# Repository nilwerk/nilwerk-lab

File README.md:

# nilwerk-lab

Engineering workspace for Nilwerk's agent team. Private.

- **How the team works:** [`team/TEAM.md`](team/TEAM.md) — roles, daily cycle, Definition of Done, hard rules.
- **Roles:** [`team/roles/`](team/roles/)
- **Daily reports:** [`team/reports/`](team/reports/)
- **First project:** [`projects/plant-monitor/`](projects/plant-monitor/) — task status lives in the Google Sheet *Plant Monitor – Project Plan*, not here.

Agents work on `agent/<role>/<task-id>` branches and open PRs. Only Arsany merges to `main`.

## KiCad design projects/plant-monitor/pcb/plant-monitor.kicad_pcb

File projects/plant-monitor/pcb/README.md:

# PCB (Plan 4.P1: schematic) — Emil (PCB Designer)

KiCad 9 project `plant-monitor.kicad_pro` / `plant-monitor.kicad_sch` (one A1 sheet, net labels at every pin, no wires).
It is **generated** from [`design.py`](design.py) by [`gen_schematic.py`](gen_schematic.py) (no GUI was available);
[`check_netlist.py`](check_netlist.py) is the independent netlist/BOM/sleep check. Requirements: NFR-01 (best and typical case >= 3 months, worst case > 1 month; relaxed by Arsany 2026-11-08), NFR-12 (<= 50 uA, target 25 uA, A-027).
Layout is 4.P2, **slice 1 done (placement, not routed), slice 2 done (real footprints for U1/J1/J2/SW/standard parts, vias out of pads, antenna check in CI), slice 3 done (U5/U6 footprints from LCSC/EasyEDA data, power section routed except 3 connections; signal routing, GND pour and 3V3 distribution still open, not fab-ready)**: see [`layout-4P2.md`](layout-4P2.md); the board is generated by [`gen_pcb.py`](gen_pcb.py), checked by [`check_layout.py`](check_layout.py). Nothing was ordered.

**Update 2026-11-08 (Arsany's answers):** A-034 the cell is the **EEMB LP603449-PCM from Amazon.de (ASIN B08FD39Y5R)**; NFR-01 relaxed; **A-045 Option A** and **A-046 Option A** applied (below). Cell facts and what is still unverified: [`../hardware/bom/cell-decision-A034.md`](../hardware/bom/cell-decision-A034.md).

## Status of the checks

| Check | Result |
|---|---|
| KiCad ERC (`kicad-cli sch erc`) | Runs in CI (job `pcb`, KiCad 9 container) on every push of this PR; not available in the agent session. 0 violations at error level on head a0a4c90, CI run 42576375828 (job `pcb`, job 129024963788). |
| `python3 -I check_netlist.py` | all PASS (nets rebuilt from the file = model, no unconnected pin, no 1-pin net, BOM draft lcsc/qty = schematic, R9, strap pins, sleep sum) |
| KiCad DRC (`kicad-cli pcb drc`) | CI job `pcb`: 0 violations at error level on the 4.P2 slice-1 head (placed, not routed, placeholder footprints; unconnected items are warning-level, not in the error-level report; `unconnected_items` = warning, to be reverted when routing starts): [`layout-4P2.md`](layout-4P2.md). |
| `/usr/bin/python3 -I check_layout.py` | 18/18 PASS (own geometry check of the board file, not KiCad DRC) |
| Simulations | **LDO dropout: RUN** (ngspice 42 via `apt-get install ngspice`, `sim/ldo_dropout.py`, `sim/ldo_dropout.png`): V(3V3) stays >= 3.05 V in every modelled case at the 3.4 V warning point (limit 3.0 V = VDD33 min), fails at <= 3.3 V cell with 0.30 ohm / pessimistic dropout, see `layout-brief.md` section 6. Divider, soil front end, charger thresholds, USB inrush: **NOT RUN.** |

## Charge current R9 (A-034 decided 2026-11-08)

Cell: EEMB LP603449-PCM, 1000 mAh minimum (1100 typical), maximum charging current 1100 mA, charge 0 to 45 C (Amazon.de listing, A+ text). `design.py` block `CHARGE CURRENT`: `CELL_MIN_MAH`, `CELL_MAX_CHARGE_MA`, `R9_OHM`, `R9_LCSC`. Recomputed for this cell: R_PROG = 1100 / I_BAT (TP4056 datasheet p. 9), target <= 0.5C = 500 mA. **R9 stays 2.4k (C22940): 458 mA = 0.46C of the minimum capacity (0.42C of typical); with the TP4056's +15 % tolerance 527 mA = 0.53C, below the 1100 mA cell maximum.** 2.2k would give exactly 0.50C (500 mA) but its LCSC number is not looked up and the USB 2.0 budget (500 mA, open point 3) has no room for it. USB draw is about 458 + 10 mA with no power path (A-046): inside 500 mA nominally; at +15 % tolerance (527 mA) the port limit is exceeded, accepted risk, see open point 3. `check_netlist.py` asserts <= 0.5C and tolerance <= cell maximum.

## Cell connector, NTC / TEMP (decided cell)

J2 = JST PH 2-pin (C295747): pin 1 = CELL+ (VBAT), pin 2 = CELL- (CELL_NEG). The listing says "JST plug" (picture 3 shows it) but **does not state the pitch or the polarity**: PH 2.0 mm is assumed and **unverified**; read it off the plug or the listing photo before ordering mating parts. An Amazon review of this listing reports a reversed plug: **check polarity with a meter before the first connection.** The listing mentions no NTC, so **TP4056 TEMP stays tied to GND (sense disabled, datasheet p.7)** and cold/hot charging (0 to 45 C only) is not enforced by the board. The Jauch 3-pin variant J2b (C564183) is not used.

## Sleep-current path and pin map

Generated: [`pinmap-sleep.md`](pinmap-sleep.md). Typical **21.6 uA**, worst **39.6 uA** vs NFR-12 25 / 50 uA (after A-045: +2.1 uA permanent divider), mostly assumptions.

## Differences against the BOM draft (hardware/bom)

**Synced 2026-11-08 (branch `agent/pcb/bom-sync`):** `hardware/bom/bom-draft.csv` now has Q2 deleted, R3-R5 qty 3, R13/R14 (4.7k I2C), R15 (1k DW01A CS), R16 (10k GPIO2) and B1 = the decided EEMB LP603449-PCM; `check_netlist.py` has no declared differences left (every LCSC number and quantity equals the schematic, and `bom.csv` equals the schematic). Footprints for SW1-3, U5, U6, E1 are custom names still to be drawn.

## Open points

1. ~~Battery sense, Q2 off: BAT_SENS floats to VBAT~~ **Closed (A-045 Option A, Arsany 2026-11-08):** Q2 and R6 dropped, R7/R8 1M+1M permanent divider (2.1 uA at 4.2 V), BAT_SENS never above 2.1 V, IO1 free.
2. **TEMP / cold charging:** cell may be charged 0-45 C only; the decided cell lists no NTC, TEMP grounded. Mitigation options: a GPIO on CE (CE internal default not read) or accept (indoor charging).
3. **USB 500 mA:** 458 mA charge + board load is at the USB 2.0 limit; TP4056 dissipates 0.78 W at 5 V in / 3.3 V cell (thermal foldback, not simulated).
4. **Double protection (decision for Arsany, recommendation: delete U4/Q1/R15/C9 once the PCM on the received cell is confirmed).** Numbers (`hardware/bom/bom_calc.py` variant D, live prices 2026-11-08): saves 2 Extended parts and 4 pieces; BOM at 3 boards 20.04 -> 17.86 USD/board (-2.18, of which -2.05 is JLC loading fee 2 x 3.07 / 3, -0.13 parts), at 1k boards 4.05 -> 3.96 (-0.09; U4 0.017 + Q1 0.060 + R15 0.001 + C9 0.009 USD at the 1k price breaks). Sleep: -3.05 uA typ (DW01A 3 + 8205A 0.05, both assumptions, datasheet Iq not read) and -7 uA worst: 21.6 -> 18.6 uA typ, 39.6 -> 32.6 uA worst (NFR-12 target 25 uA gets 1.35x margin instead of 1.16x). Battery life: about +1 % (typical 4.3 -> 4.35 months, worst +0.01), small. Also removes a series Rds(on) (8205A, value unread) from the 350 mA TX path = better LDO headroom. Risk of deleting: the cell's PCM exists only as a listing claim (OC/OD/over-current/short; thresholds, PCM IC, IEC 62133 not stated; one review reports a reversed plug, so QC varies); a second protection is the only protection if that PCM is faulty or missing, and a lithium pouch without any protection is a fire risk. Why not done now: not clearly safe without the cell in hand (nobody has read the PCM board or tested its cutoffs), and it is Arsany's call. Recommended path: keep v1 schematic and layout unchanged for the first 3 prototypes (no layout exists yet, so deleting later costs one regenerate + one BOM line change), Peter reads the PCM marking and measures over-discharge cutoff and short-circuit trip on one cell (5.x), then delete for the 1k design. If Arsany wants it deleted now: remove U4, Q1, R15, C9 in `design.py` and tie CELL_NEG to GND (about 20 min incl. regenerate and checks).
5. ~~GPIO2 strap left unconnected~~ **Closed (Theo C4):** R16 10k to 3V3 on GPIO2 (Espressif datasheet v2.2 s.4.1 recommends a pull-up). No sleep current.
6. **USB data:** BOM says "power only"; D+/D- are wired to IO19/IO18 (USB Serial/JTAG) so D1 is meaningful. Arsany/Mira to confirm (affects flashing).
7. **Pin numbers: all now checked against datasheets** (see Fix round). Remaining: BH1750 DVI is tied directly to VCC; the datasheet wants DVI low >= 1 us after VCC (reset), example RC 1k/1uF. Decide in 4.P2 (add RC or accept and re-init in firmware).
8. Soil: electrode capacitance still assumed, no electrode ESD, wet/salty soil loading, U7 supply GPIO must be held low in deep sleep (firmware).
9. No power path (**A-046 Option A, Arsany 2026-11-08: accepted for v1; the board needs a cell**, document in the user guide: with USB only and no cell it does not run, and "charge complete" can be late while Wi-Fi is active): No VBUS fuse/TVS (only USBLC6). No DW01A VCC filter resistor. No VBUS-present or CHRG sense to a GPIO.
10. LDO Iq is 8 uA typ (datasheet, PS mode, 0.1 mA load; 18 uA max), 6 uA above the power-budget typical (2 uA, assumption A). Cost: 6 uA x 24 h = 0.144 mAh/day (about 53 mAh/year). The sleep sum in `pinmap-sleep.md` already uses 8 uA. `hardware/power-budget` keeps its 2 uA baseline rows; since 2026-11-08 it also has "as-built sleep" rows (LDO 8 uA, divider 2.1 uA, same sums as `pinmap-sleep.md`), see power-budget.md section 12.
11. ~~Cell A-034 decision~~ **Closed 2026-11-08:** EEMB LP603449-PCM; R9 recomputed (stays 2.4k). `firmware/main/board.h` does not exist; this pin table is the proposal. **IO1 is free (was BAT_SENS_EN): Mira must not drive it as a divider switch.**

## Fix round for Theo's review (PR #41, C1-C8)

| Item | Result |
|---|---|
| C1 AHT20 U5 | LCSC C2757850 resolved through the LCSC API (`wmsc.lcsc.com`) and its datasheet (Aosong/ASAIR, 2024-07, Table 5 and Figure 1): **6-pin DFN 3.0 x 3.0 x 1.0 mm**, 1 NC, 2 VDD, 3 SCL, 4 SDA, 5 GND, 6 NC. Symbol fixed (`design.py`), `pin_verified` now true, checked by `check_netlist.py`. Footprint `NW:AHT20_DFN-6_3x3` still to be drawn in 4.P2. Stock 32649 at the time of the call. |
| C2 pins | Read from the LCSC-linked datasheets: **U2** XC6220 SOT-25 (VIN 1, VSS 2, CE 3, NC 4, VOUT 5), **U4** DW01A (1 OD, 2 VM = CS, 3 OC, 4 TD, 5 VCC, 6 GND), **Q1** 8205A TSSOP-8 (package drawing: 1 D1, 2-3 S1, 4 G1, 5 G2, 6-7 S2, 8 D2; no numbered table in the datasheet, read from the drawing), **U6** BH1750 (1 VCC, 2 ADDR, 3 GND, 4 SDA, 5 DVI, 6 SCL), **J1** HRO TYPE-C-31-M-12 (signal-to-pad table; shield pad numbers belong to the footprint). Also checked: U3 TP4056 (1 TEMP, 2 PROG, 3 GND, 4 VCC, 5 BAT, 6 STDBY, 7 CHRG, 8 CE), U7 SN74LVC1G14 DBV (1 NC, 2 A, 3 GND, 4 Y, 5 VCC), D1 USBLC6-2SC6. All match the schematic. U1 was verified by Theo. `pin_verified=False` was gone from every part after 4.P1; 4.P2 sets it again for SW1-SW3, U5, U6, J1 until the placed footprints are compared with the drawings (`layout-4P2.md`). |
| C4 GPIO2 | R16 10k 3V3 to GPIO2 added (declared addition, BOM qty of C25804 5). |
| C5 LDO dropout sim (superseded by the next row) | *Original first-pass status, kept for traceability:* not run at the time, hand estimate only: datasheet gives 60 mV typ dropout at 300 mA (3.3 V version; the table row is ambiguous), the 3.4 V warning leaves 100 mV, so at a ~350 mA TX peak typ headroom is about 30 mV before the cell resistance drop (0.15 ohm x 0.35 A = 52 mV, assumed). That is negative margin: the rail may sag to roughly 3.25-3.3 V, which stays above the C3 brown-out level but this needs the real sim and the real cell resistance (4.P3). Do not take the estimate as a pass. LDO Iq 8 uA vs 2 uA in the budget: see open point 10. |
| C5 follow-up 2026-11-08 | Simulated: the hand estimate's conclusion (rail below 3.3 V) is right but the limit is 3.0 V, and the margin there is +0.05 to +0.27 V at 3.4 V cell voltage (`sim/ldo_dropout.txt`). |
| C8 caption | Corrected (6.3 agent min, PR link, persona, no ratio). |
| C3, C6 | Decisions below, not changed. |

## Decisions (answered by Arsany 2026-11-08)

**D-C3 / A-045: ANSWERED 2026-11-08, Option A approved.** Q2 and R6 dropped, R7/R8 1M+1M stay as a permanent divider (4.2 V / 2 MOhm = 2.1 uA, about 0.05 mAh/day; total typical 21.6 uA under the 25 uA target, worst 39.6 uA under the 50 uA NFR-12 limit). BAT_SENS never exceeds 2.1 V on IO0; IO1 is free. Applied in `design.py`, the schematic, `bom.csv`, `pinmap-sleep.md`. (Option B, a high-side P-FET switch, was not chosen.)

**D-C6 / A-046: ANSWERED 2026-11-08, Option A approved.** No power path in v1. **The board needs a cell to run** (USB alone, with no cell connected, does not power it reliably, and charge termination can be late while the board is awake and drawing current; the sleep load of about 22 uA is far below the TP4056 termination threshold of about 46 mA, so it matters only when awake). To go into the user guide and the work order for Peter (power the board only with the cell fitted). (Option B, a P-FET ideal diode, was not chosen.)

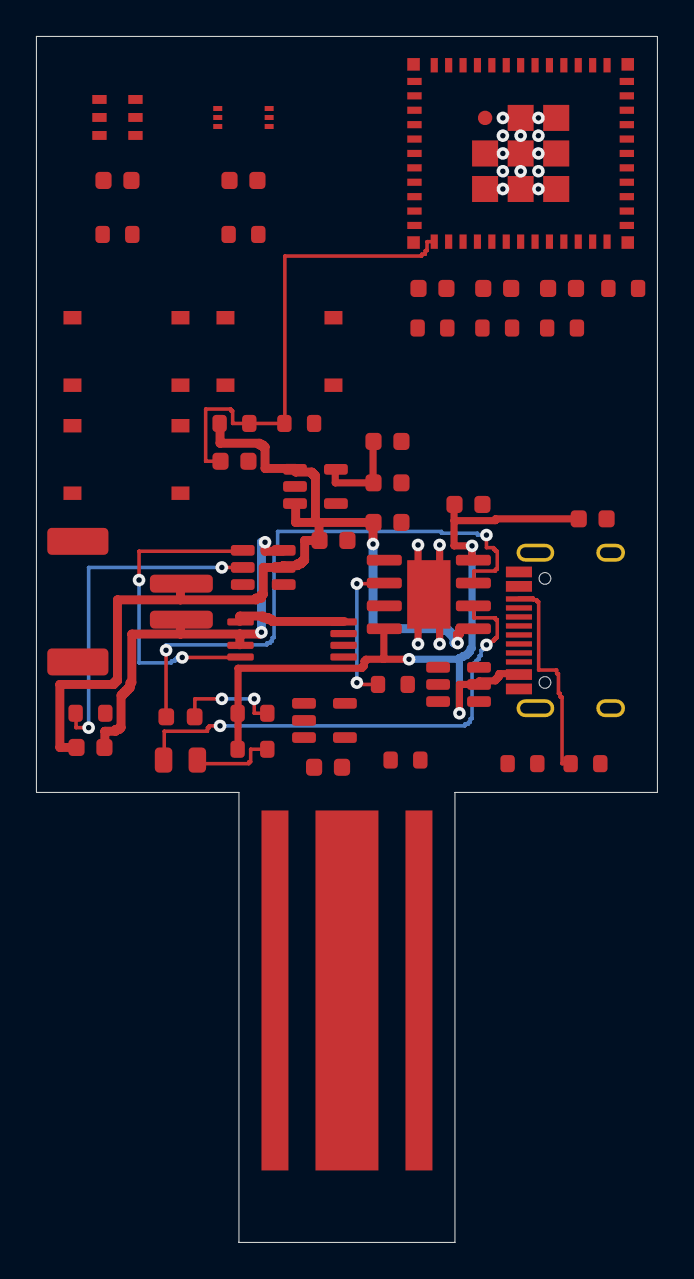
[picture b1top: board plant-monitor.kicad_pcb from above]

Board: 2 copper layers, 34.5 x 67.0 mm, 46 parts (0 on the bottom side), 29 nets.

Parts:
C1, C2, C3, C4: 10uF; C_0603_1608Metric
C5, C6, C7, C8, C9, C10, C11: 100nF; C_0603_1608Metric
C12, C13: 1uF; C_0603_1608Metric
C14: 22uF; C_0603_1608Metric
D1: USBLC6-2SC6; SOT-23-6
D2: LED red CHRG; LED_0603_1608Metric
D3: LED green STDBY; LED_0805_2012Metric
E1: Soil probe electrodes (PCB copper); SOIL_PROBE_STAKE
J1: USB-C (power + USB-JTAG data); USB_C_Receptacle_HRO_TYPE-C-31-M-12
J2: JST PH 2-pin (cell); JST_PH_S2B-PH-SM4-TB_1x02-1MP_P2.00mm_Horizontal
Q1: 8205A dual N-MOSFET; TSSOP-8_4.4x3mm_P0.65mm
R1, R2: 5.1k; R_0603_1608Metric
R3, R4, R5, R16: 10k; R_0603_1608Metric
R7, R8: 1M; R_0603_1608Metric
R9: 2.4k; R_0603_1608Metric
R10, R11, R15: 1k; R_0603_1608Metric
R12: 470k; R_0603_1608Metric
R13, R14: 4.7k; R_0603_1608Metric
SW1: BOOT; SW_TS-1187A-B-A-B_5.1x5.1
SW2: RESET; SW_TS-1187A-B-A-B_5.1x5.1
SW3: FACTORY RESET (pinhole); SW_TS-1187A-B-A-B_5.1x5.1
U1: ESP32-C3-MINI-1-N4; ESP32-C3-MINI-1
U2: XC6220B331MR-G (3.3 V); SOT-23-5
U3: TP4056; SOIC-8-1EP_3.9x4.9mm_P1.27mm_EP2.41x3.81mm
U4: DW01A; SOT-23-6
U5: AHT20; AHT20_DFN-6_3x3
U6: BH1750FVI; WSOF-6_BH1750FVI
U7: SN74LVC1G14DBVR; SOT-23-5

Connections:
3V3: C4.1, C5.1, C6.1, C7.1, C13.1, C14.1, R3.1, R4.1, R5.1, R13.1, R14.1, R16.1, U1.3, U2.5, U5.2, U6.1, U6.5
BAT_SENS: C11.1, R7.2, R8.1, U1.12
BOOT_N: R5.2, SW1.1, SW1.2, U1.23
CC1: J1.A5, R1.1
CC2: J1.B5, R2.1
CELL_NEG: C9.2, J2.2, Q1.2, Q1.3, U4.6
CHRG_N: D2.1, U3.7
DW_CS: R15.1, U4.2
DW_OC: Q1.5, U4.3
DW_OD: Q1.4, U4.1
EN: C12.1, R3.2, SW2.1, SW2.2, U1.8
FACTORY_RST_N: SW3.1, SW3.2, U1.19
FET_MID: Q1.1, Q1.8
GND: C1.2, C2.2, C3.2, C4.2, C5.2, C6.2, C7.2, C8.2, C10.2, C11.2, C12.2, C13.2, C14.2, D1.2, E1.2, J1.A1, J1.A12, J1.B1, J1.B12, J1.S1, Q1.6, Q1.7, R1.2, R2.2, R8.2, R9.2, R15.2, SW1.3, SW1.4, SW2.3, SW2.4, SW3.3, SW3.4, U1.1, U1.2, U1.11, U1.14, U1.36, U1.37, U1.38, U1.39, U1.40, U1.41, U1.42, U1.43, U1.44, U1.45, U1.46, U1.47, U1.48, U1.49, U1.50, U1.51, U1.52, U1.53, U2.2, U3.1, U3.3, U3.9, U5.5, U6.2, U6.3, U7.3
GPIO2_STRAP: R16.2, U1.5
GPIO8_STRAP: R4.2, U1.22
I2C_SCL: R14.2, U1.21, U5.3, U6.6
I2C_SDA: R13.2, U1.20, U5.4, U6.4
LED_CHRG_A: D2.2, R10.2
LED_STDBY_A: D3.2, R11.2
PROG: R9.1, U3.2
SOIL_OUT: R12.1, U1.18, U7.4
SOIL_PROBE: E1.1, R12.2, U7.2
SOIL_PWR: C8.1, U1.6, U7.5
STDBY_N: D3.1, U3.6
USB_DN: D1.3, D1.4, J1.A7, J1.B7, U1.26
USB_DP: D1.1, D1.6, J1.A6, J1.B6, U1.27
VBAT: C2.1, C3.1, C9.1, J2.1, R7.1, U2.1, U2.3, U3.5, U4.5
VBUS: C1.1, C10.1, D1.5, J1.A4, J1.A9, J1.B4, J1.B9, R10.1, R11.1, U3.4, U3.8

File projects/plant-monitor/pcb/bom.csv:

Designator,Qty,Value,Footprint,LCSC,MPN,FootprintStatus,PinMapStatus,Note
"C1,C2,C3,C4",4,10uF,Capacitor_SMD:C_0603_1608Metric,C19702,CL10A106KP8NNNC,kicad-library-name,standard-pinout,U1 bulk
"C12,C13",2,1uF,Capacitor_SMD:C_0603_1608Metric,C15849,CL10A105KB8NNNC,kicad-library-name,standard-pinout,EN reset delay
C14,1,22uF,Capacitor_SMD:C_0603_1608Metric,C59461,CL10A226MQ8NRNC,kicad-library-name,standard-pinout,LDO output / Wi-Fi burst
"C5,C6,C7,C8,C9,C10,C11",7,100nF,Capacitor_SMD:C_0603_1608Metric,C14663,CC0603KRX7R9BB104,kicad-library-name,standard-pinout,U1 decoupling
D1,1,USBLC6-2SC6,Package_TO_SOT_SMD:SOT-23-6,C7519,USBLC6-2SC6,kicad-library-name,standard-pinout,ESD on USB (NFR-08); both I/O pins of a channel on the same net
D2,1,LED red CHRG,LED_SMD:LED_0603_1608Metric,C2286,KT-0603R,kicad-library-name,standard-pinout,pin 1 = cathode assumed; check footprint polarity
D3,1,LED green STDBY,LED_SMD:LED_0805_2012Metric,C2297,KT-0805G,kicad-library-name,standard-pinout,pin 1 = cathode assumed
J1,1,USB-C (power + USB-JTAG data),Connector_USB:USB_C_Receptacle_HRO_TYPE-C-31-M-12,C165948,TYPE-C-31-M-12,kicad-library-name,signal-map-from-4.P1-not-checked-vs-4.P2-drawing,BOM calls it power only; D+/D- are wired to IO19/IO18 (USB Serial/JTAG) so D1 has a job: OPEN POINT 6. Signal-to-pad map as recorded in 4.P1 from the HRO TYPE-C-31-M-12 drawing (LCSC C165948); shield pad numbers belong to the 4.P2 footprint. 4.P2 flag: pin_verified=False because the placed footprint has not been compared with that drawing (4.P2 slice 1 did not do it).
J2,1,JST PH 2-pin (cell),Connector_JST:JST_PH_S2B-PH-SM4-TB_1x02-1MP_P2.00mm_Horizontal,C295747,S2B-PH-SM4-TB(LF)(SN),kicad-library-name,standard-pinout; plug pitch and polarity UNVERIFIED (A-053),"Cell EEMB LP603449-PCM (A-034): listing says 'JST plug', PITCH AND POLARITY UNVERIFIED (read the plug label / photo 3 on the Amazon listing: PH 2.0 mm is assumed). CHECK PLUG POLARITY with a meter before first connection (an Amazon review of this listing reports a reversed plug). 2-pin cell, no NTC: TP4056 TEMP stays tied to GND. Variant J2b (3-pin Molex C564183, Jauch cell) is NOT used."
Q1,1,8205A dual N-MOSFET,Package_SO:TSSOP-8_4.4x3mm_P0.65mm,C5148694,8205A,kicad-library-name,standard-pinout,"FET1 (S1 = B-) gate = OD blocks discharge; FET2 (S2 = P- = GND) gate = OC blocks charge. LCSC C5148694 (HXY) is TSSOP-8; pin map 1 D1, 2-3 S1, 4 G1, 5 G2, 6-7 S2, 8 D2 read from the package drawing in the datasheet (no numbered table printed)."
"R1,R2",2,5.1k,Resistor_SMD:R_0603_1608Metric,C23186,0603WAF5101T5E,kicad-library-name,standard-pinout,USB-C sink Rd
"R10,R11,R15",3,1k,Resistor_SMD:R_0603_1608Metric,C21190,0603WAF1001T5E,kicad-library-name,standard-pinout,CHRG LED series; no current when USB is unplugged
R12,1,470k,Resistor_SMD:R_0603_1608Metric,C23178,0603WAF4703T5E,kicad-library-name,standard-pinout,"timing resistor, tune on the real stake (5.x)"
"R13,R14",2,4.7k,Resistor_SMD:R_0603_1608Metric,C23162,0603WAF4701T5E,kicad-library-name,standard-pinout,ADDED by 4.P1 (BOM draft has no I2C pull-ups). LCSC number from memory: unverified
"R3,R4,R5,R16",4,10k,Resistor_SMD:R_0603_1608Metric,C25804,0603WAF1002T5E,kicad-library-name,standard-pinout,EN pull-up; EN RC = R3 x C12 = 10 ms
"R7,R8",2,1M,Resistor_SMD:R_0603_1608Metric,C22935,0603WAF1004T5E,kicad-library-name,standard-pinout,"divider top (permanent, A-045 Option A)"
R9,1,2.4k,Resistor_SMD:R_0603_1608Metric,C22940,0603WAF2401T5E,kicad-library-name,standard-pinout,R_PROG = 1100/I_BAT -> 458 mA = 0.46C of 1000 mAh (cell max charge 1100 mA). A-034 decided: see CHARGE CURRENT block in design.py
SW1,1,BOOT,NW:SW_TS-1187A-B-A-B_5.1x5.1,C318884,TS-1187A-B-A-B,to-draw-in-4.P2,signal-map-from-4.P1-not-checked-vs-4.P2-drawing,BOOT (GPIO9 low at reset = download mode)
SW2,1,RESET,NW:SW_TS-1187A-B-A-B_5.1x5.1,C318884,TS-1187A-B-A-B,to-draw-in-4.P2,signal-map-from-4.P1-not-checked-vs-4.P2-drawing,RESET (EN low)
SW3,1,FACTORY RESET (pinhole),NW:SW_TS-1187A-B-A-B_5.1x5.1,C318884,TS-1187A-B-A-B,to-draw-in-4.P2,signal-map-from-4.P1-not-checked-vs-4.P2-drawing,Pinhole factory reset on IO5 (RTC GPIO: wakes from deep sleep); firmware enables the internal pull-up
U1,1,ESP32-C3-MINI-1-N4,RF_Module:ESP32-C3-MINI-1,C2838502,ESP32-C3-MINI-1-N4,kicad-library-name,standard-pinout,FR-D01. Pin numbers verified by Theo against Espressif ESP32-C3-MINI-1 datasheet v2.2 Table 3-1 (PR #41 review). IO2 pulled up by R16; IO10/UART unused.
U2,1,XC6220B331MR-G (3.3 V),Package_TO_SOT_SMD:SOT-23-5,C86534,XC6220B331MR-G,kicad-library-name,standard-pinout,"Iq 8 uA typ (datasheet, PS mode, IOUT 0.1 mA; 18 uA max A/B series). CE tied to VIN. SOT-25 pins verified: VIN 1, VSS 2, CE 3, NC 4, VOUT 5."
U3,1,TP4056,Package_SO:SOIC-8-1EP_3.9x4.9mm_P1.27mm_EP2.41x3.81mm,C16581,TP4056-42-ESOP8,kicad-library-name,standard-pinout,"TEMP tied to GND = temperature sense disabled (datasheet p.7): the decided cell (EEMB LP603449-PCM, A-034) lists no NTC (wire count not stated in the listing). CE tied high = always enabled."
U4,1,DW01A,Package_TO_SOT_SMD:SOT-23-6,C351410,DW01A,kicad-library-name,standard-pinout,"Cell protection. Pins verified against LCSC C351410 datasheet (pin 2 is called VM there = the CS/sense input). The decided cell has its own PCM, so U4/Q1 are a second, redundant protection (open point 4: keep or delete, decision for Arsany)."
U5,1,AHT20,NW:AHT20_DFN-6_3x3,C2757850,AHT20,lcsc-easyeda-geometry-UNVERIFIED-vs-drawing,signal-map-from-4.P1-not-checked-vs-4.P2-drawing,"Fix for Theo C1: LCSC C2757850 (Aosong/ASAIR AHT20, datasheet 2024-07 linked from the LCSC page) is a 6-pin DFN 3.0 x 3.0 x 1.0 mm: 1 NC, 2 VDD, 3 SCL, 4 SDA, 5 GND, 6 NC (Table 5, top view). Custom footprint still to be drawn in 4.P2 from the datasheet figure 1. I2C 0x38. 4.P2 flag: pin_verified=False until the placed footprint is compared with the drawing."
U6,1,BH1750FVI,NW:WSOF-6_BH1750FVI,C78960,BH1750FVI-TR,lcsc-easyeda-geometry-UNVERIFIED-vs-drawing,signal-map-from-4.P1-not-checked-vs-4.P2-drawing,"ADDR low = 0x23. Pins verified against LCSC C78960 datasheet (1 VCC, 2 ADDR, 3 GND, 4 SDA, 5 DVI, 6 SCL). DVI tied to VCC directly: datasheet wants DVI low >= 1 us after VCC (RC example 1k/1uF) or a reset: OPEN POINT 7, firmware must also re-init after power-up. 4.P2 flag: pin_verified=False until the placed footprint is compared with the drawing."
U7,1,SN74LVC1G14DBVR,Package_TO_SOT_SMD:SOT-23-5,C7835,SN74LVC1G14DBVR,kicad-library-name,standard-pinout,Schmitt oscillator; VCC from GPIO IO3 (must be held LOW in deep sleep). Sizing: hardware/soil-frontend/soil_frontend.py

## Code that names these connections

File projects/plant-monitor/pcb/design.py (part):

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add("U1", "ESP32-C3-MINI-1", "ESP32-C3-MINI-1-N4", "RF_Module:ESP32-C3-MINI-1", "C2838502", "ESP32-C3-MINI-1-N4",
    [("3", "3V3", "3V3", "L"), ("8", "EN", "EN", "L"),
     ("12", "IO0/ADC1_0", "BAT_SENS", "L"), ("13", "IO1", "NC", "L"),
     ("5", "IO2 (strap)", "GPIO2_STRAP", "L"), ("6", "IO3", "SOIL_PWR", "L"), ("18", "IO4", "SOIL_OUT", "L"),
     ("19", "IO5", "FACTORY_RST_N", "L"),
     ("20", "IO6", "I2C_SDA", "R"), ("21", "IO7", "I2C_SCL", "R"), ("22", "IO8 (strap)", "GPIO8_STRAP", "R"),
     ("23", "IO9 (strap)", "BOOT_N", "R"), ("16", "IO10", "NC", "R"),
     ("26", "IO18/USB_D-", "USB_DN", "R"), ("27", "IO19/USB_D+", "USB_DP", "R"),
     ("30", "RXD0/IO20", "NC", "R"), ("31", "TXD0/IO21", "NC", "R")]
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cap("C4", *C10U[:1], C10U[1], C10U[2], "3V3", "GND", B, "U1 bulk")
res("R3", *R10K, "3V3", "EN", B, "EN pull-up; EN RC = R3 x C12 = 10 ms")
cap("C12", "1uF", "C15849", "CL10A105KB8NNNC", "EN", "GND", B, "EN reset delay")
res("R4", *R10K, "3V3", "GPIO8_STRAP", B, "GPIO8 strap high (needed for download boot)")
res("R5", *R10K, "3V3", "BOOT_N", B, "GPIO9 strap: high = SPI boot, BOOT switch pulls low")
res("R16", *R10K, "3V3", "GPIO2_STRAP", B, "ADDED by 4.P1 fix round (Theo C4): ESP32-C3-MINI-1 datasheet v2.2 s.4.1 recommends a pull-up on GPIO2 (glitches); node at the rail, no sleep current")
add("SW1", "SW4P", "BOOT", "NW:SW_TS-1187A-B-A-B_5.1x5.1", "C318884", "TS-1187A-B-A-B",
    [("1", "1", "BOOT_N", "L"), ("2", "2", "BOOT_N", "L"), ("3", "3", "GND", "R"), ("4", "4", "GND", "R")],
    "BOOT (GPIO9 low at reset = download mode)", custom_fp=True, pin_verified=False, block=B)
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cap("C2", *C10U, "VBAT", "GND", B, "TP4056 BAT output")
res("R10", "1k", "C21190", "0603WAF1001T5E", "VBUS", "LED_CHRG_A", B, "CHRG LED series; no current when USB is unplugged")
add("D2", "LED", "LED red CHRG", "LED_SMD:LED_0603_1608Metric", "C2286", "KT-0603R",
    [("1", "K", "CHRG_N", "L"), ("2", "A", "LED_CHRG_A", "R")], "[mine, UNVERIFIED] pin 1 = cathode assumed (KT-0603R LED datasheet and footprint polarity not checked); check before the dry run", block=B)
res("R11", "1k", "C21190", "0603WAF1001T5E", "VBUS", "LED_STDBY_A", B, "STDBY LED series")
add("D3", "LED", "LED green STDBY", "LED_SMD:LED_0805_2012Metric", "C2297", "KT-0805G",
    [("1", "K", "STDBY_N", "L"), ("2", "A", "LED_STDBY_A", "R")], "[mine, UNVERIFIED] pin 1 = cathode assumed (KT-0805G LED datasheet and footprint polarity not checked); check before the dry run", block=B)
add("J2", "JSTPH2", "JST PH 2-pin (cell)", "Connector_JST:JST_PH_S2B-PH-SM4-TB_1x02-1MP_P2.00mm_Horizontal", "C295747",
    "S2B-PH-SM4-TB(LF)(SN)",
    [("1", "CELL+", "VBAT", "R"), ("2", "CELL-", "CELL_NEG", "R"), ("MP1", "MP", "NC", "R"), ("MP2", "MP", "NC", "R")],
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
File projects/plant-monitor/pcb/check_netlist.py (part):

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check(not any(p.ref in ("Q2", "R6") for p in D.PARTS) and not any("BAT_SENS_EN" in [x[2] for x in p.pins] for p in D.PARTS),
      "A-045 Option A: no Q2, no R6, no BAT_SENS_EN net")
r7, r8 = (next(p for p in D.PARTS if p.ref == r) for r in ("R7", "R8"))
check({x[2] for x in r7.pins} == {"VBAT", "BAT_SENS"} and {x[2] for x in r8.pins} == {"BAT_SENS", "GND"} and r7.value == r8.value == "1M",
      "A-045: battery divider R7 (VBAT-BAT_SENS) + R8 (BAT_SENS-GND), 1M + 1M permanent: BAT_SENS max 2.1 V at 4.2 V")
tp = next(p for p in D.PARTS if p.ref == "U3")
check(any(x[1] == "TEMP" and x[2] == "GND" for x in tp.pins), "TP4056 TEMP tied to GND (the decided cell has no NTC)")

# ---------------- 5 strapping / pin sanity ----------------
u1 = {n: (nm, net) for n, nm, net, s in next(p for p in D.PARTS if p.ref == "U1").pins}
check(u1["23"][1] == "BOOT_N" and any(p.ref == "R5" and ("3V3" in [x[2] for x in p.pins]) and ("BOOT_N" in [x[2] for x in p.pins]) for p in D.PARTS),
      "GPIO9 (strap) has pull-up R5 and BOOT switch to GND")
check(u1["22"][1] == "GPIO8_STRAP" and any(p.ref == "R4" for p in D.PARTS), "GPIO8 (strap) pulled high by R4")
check(u1["5"][1] == "GPIO2_STRAP" and any(p.ref == "R16" and p.value == "10k" and {x[2] for x in p.pins} == {"3V3", "GPIO2_STRAP"} for p in D.PARTS),
      "GPIO2 (strap) pulled up to 3V3 by R16 10k (Espressif datasheet v2.2 s.4.1)")
u5 = {n: net for n, nm, net, s in next(p for p in D.PARTS if p.ref == "U5").pins}
check(u5 == {"1": "NC", "2": "3V3", "3": "I2C_SCL", "4": "I2C_SDA", "5": "GND", "6": "NC"}, "U5 AHT20 6-pin DFN map equals datasheet Table 5 (NC,VDD,SCL,SDA,GND,NC)")
gpio_used = [net for n, (nm, net) in u1.items() if nm.startswith("IO") and net != "NC"]
check(len(gpio_used) == len(set(gpio_used)), f"each GPIO net used once: {len(gpio_used)}")
check(all(n in (0, 1, 2, 3, 4, 5) for n in [int(re.match(r'IO(\d+)', nm)[1]) for n, (nm, net) in u1.items() if net in ("SOIL_PWR", "FACTORY_RST_N", "BAT_SENS")]),
      "pins that must hold/wake in deep sleep (IO0..IO5 = RTC GPIO): BAT_SENS, SOIL_PWR, FACTORY_RST_N")

# ---------------- 6 sleep budget vs NFR-12 ----------------
SLEEP = D_SLEEP = [  # (path, typ uA, worst uA, source/status)
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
